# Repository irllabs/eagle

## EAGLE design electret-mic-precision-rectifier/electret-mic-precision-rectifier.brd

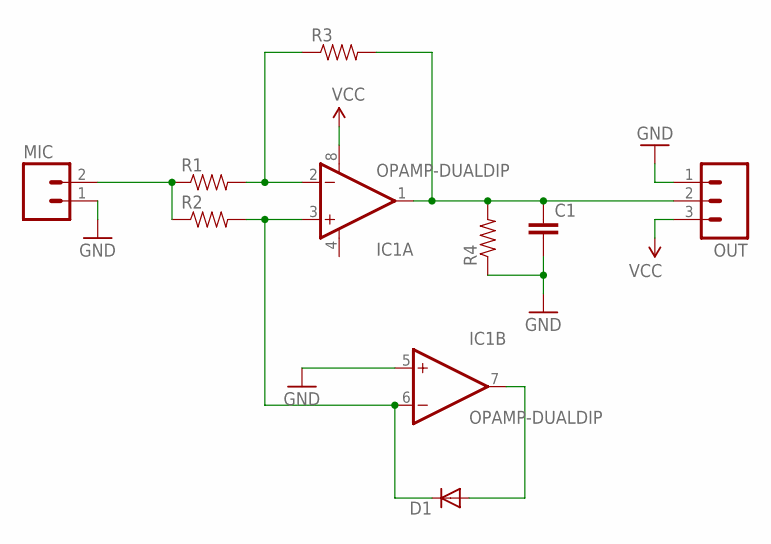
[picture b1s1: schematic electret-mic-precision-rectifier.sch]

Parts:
C1: CAP_; AXIAL-5MM
D1: DIODEPTH; DIODE-1N4001
IC1: OPAMP-DUALDIP; DIP08
MIC: M02PTH; 1X02
OUT: M03PTH; 1X03
R1, R2, R3, R4: RESISTORPTH-1/6W; 1/6W-RES

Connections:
GND: C1.P$2 (2), IC1.5 (+IN), MIC.1, OUT.1, R4.1
unnamed: C1.P$1 (1), IC1.1 (OUT), OUT.2, R3.2, R4.2
unnamed: IC1.2 (-IN), R1.2, R3.1
unnamed: D1.C, IC1.3 (+IN), IC1.6 (-IN), R2.2
unnamed: D1.A, IC1.7 (OUT)
unnamed: MIC.2, R1.1, R2.1
V-: IC1.4 (V-)
VCC: IC1.8 (V+), OUT.3

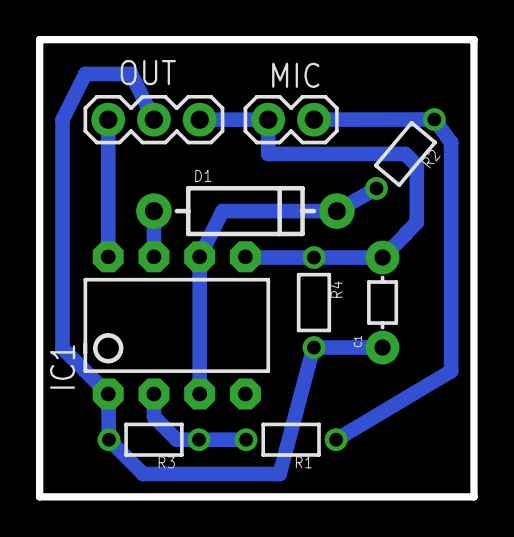
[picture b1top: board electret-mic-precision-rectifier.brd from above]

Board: 2 copper layers, 24.1 x 25.4 mm, 9 parts (0 on the bottom side), 7 nets.

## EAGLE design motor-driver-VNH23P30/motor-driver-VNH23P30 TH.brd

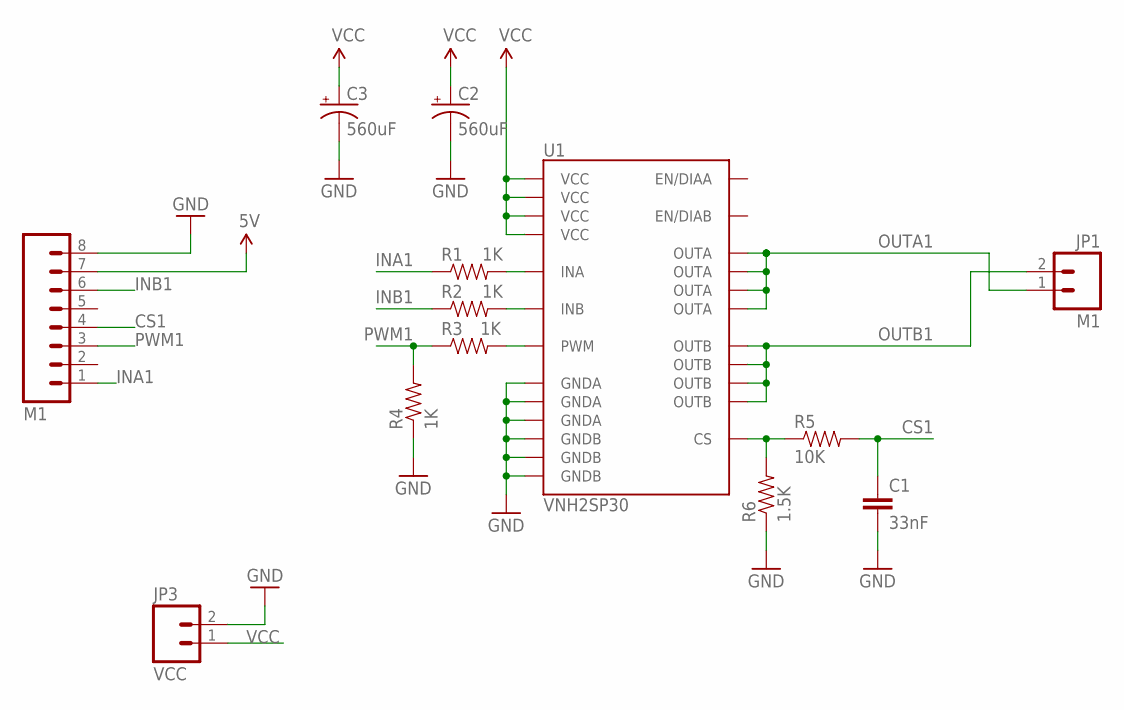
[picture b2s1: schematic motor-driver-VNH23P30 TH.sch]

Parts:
C1: 33nF; CAP-PTH-SMALLEZ
C2, C3: 560uF; CPOL-RADIAL-1000UF-25V
JP1: M1; 1X02_XTRA_BIG
JP3: VCC; 1X02_XTRA_BIG
P: M1; 1X08
R1, R2, R3, R4: 1K; 1/6W-RES
R5: 10K; 1/6W-RES
R6: 1.5K; 1/6W-RES
U1: VNH2SP30

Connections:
5V: P.7
CS1: C1.1, P.4, R5.2
GND: C1.2, C2.2 (-), C3.2 (-), JP3.2, P.8, R4.1, R6.1, U1.18 (GNDB), U1.19 (GNDB), U1.20 (GNDB), U1.26 (GNDA), U1.27 (GNDA), U1.28 (GNDA)
INA1: P.1, R1.1
INB1: P.6, R2.1
unnamed: R2.2, U1.11 (INB)
unnamed: R1.2, U1.5 (INA)
unnamed: R3.2, U1.8 (PWM)
unnamed: R5.1, R6.2, U1.9 (CS)
OUTA1: JP1.1, U1.1 (OUTA), U1.25 (OUTA), U1.30 (OUTA), U1.SLUG3 (OUTA)
OUTB1: JP1.2, U1.15 (OUTB), U1.16 (OUTB), U1.21 (OUTB), U1.SLUG2 (OUTB)
PWM1: P.3, R3.1, R4.2
VCC: C2.1 (+), C3.1 (+), JP3.1, U1.3 (VCC), U1.13 (VCC), U1.23 (VCC), U1.SLUG1 (VCC)

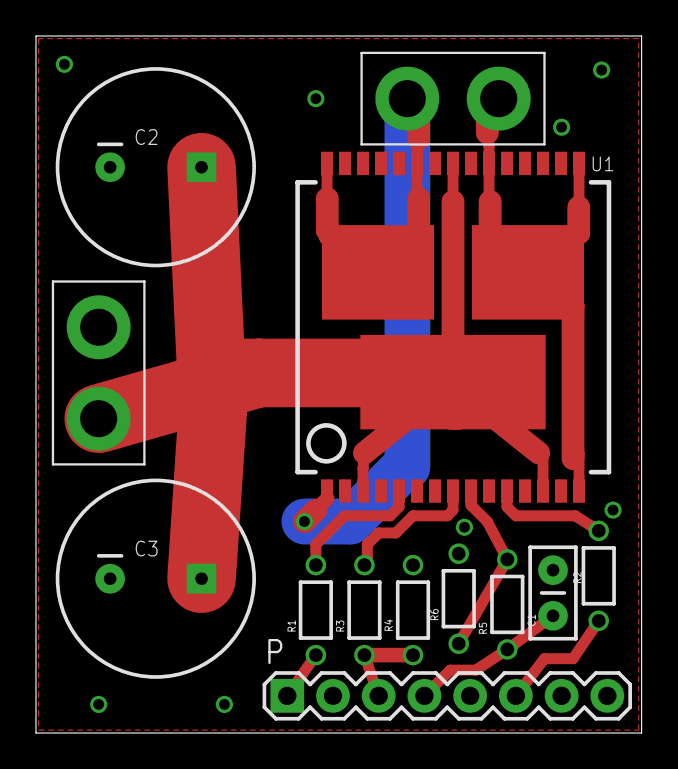
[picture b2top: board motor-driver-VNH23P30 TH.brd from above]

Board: 2 copper layers, 33.6 x 38.7 mm, 13 parts (0 on the bottom side), 12 nets.

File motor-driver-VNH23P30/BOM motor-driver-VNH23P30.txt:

Partlist exported from C:/Users/Spencer Barton/Dropbox/CMU/Activities/eagle/Spencer's Updates/motor-driver-VNH23P30/motor-driver-VNH23P30.sch at 6/30/2013 11:42:02 AM

Assembly variant: 

Part Value    Device       Package       Description        
C1   33nF     CAP1206      1206          Capacitor          
C2   560uF    CAP_POLG     PANASONIC_G   Capacitor Polarized
C3   560uF    CAP_POLG     PANASONIC_G   Capacitor Polarized
JP1  M1       M02PTH4      1X02_XTRA_BIG Header 2           
JP3  VCC      M02PTH4      1X02_XTRA_BIG Header 2           
P    M1       M081X08      1X08          Header 8           
R1   1K       RESISTOR1206 1206          Resistor           
R2   1K       RESISTOR1206 1206          Resistor           
R3   1K       RESISTOR1206 1206          Resistor           
R4   1K       RESISTOR1206 1206          Resistor           
R5   10K      RESISTOR1206 1206          Resistor           
R6   1.5K     RESISTOR1206 1206          Resistor           
U1   VNH2SP30 VNH2SP30     VNH2SP30

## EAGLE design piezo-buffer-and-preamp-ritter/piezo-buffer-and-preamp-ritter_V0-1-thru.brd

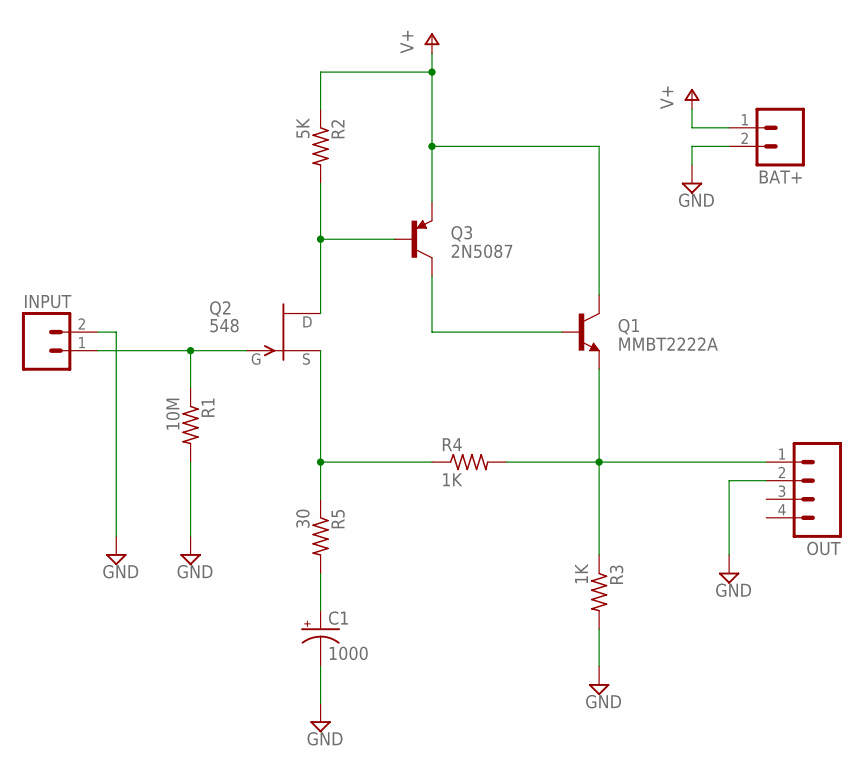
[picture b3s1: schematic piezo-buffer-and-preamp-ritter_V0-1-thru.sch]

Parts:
BAT+: M02LOCK; 1X02_LOCK
C1: 1000; CPOL-RADIAL-10UF-25V
INPUT: M02LOCK; 1X02_LOCK
OUT: M04PTH; 1X04
Q1: MMBT2222A; TO-92
Q2: 548; TO-92
Q3: 2N5087; TO-92
R1: 10M; VMTA55
R2: 5K; VMTA55
R3, R4: 1K; VMTA55
R5: 30; VMTA55

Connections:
GND: BAT+.2, C1.2 (-), INPUT.2, OUT.2, R1.2, R3.2
unnamed: INPUT.1, Q2.1 (G), R1.1
unnamed: Q2.3 (D), Q3.2 (B), R2.2
unnamed: OUT.1, Q1.1 (E), R3.1, R4.2
unnamed: Q2.2 (S), R4.1, R5.1
unnamed: Q1.2 (B), Q3.3 (C)
unnamed: C1.1 (+), R5.2
V+: BAT+.1, Q1.3 (C), Q3.1 (E), R2.1

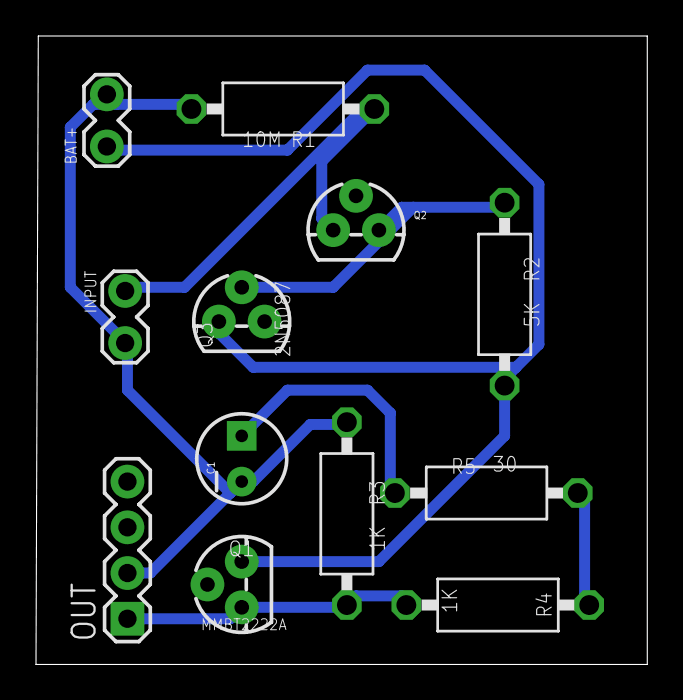
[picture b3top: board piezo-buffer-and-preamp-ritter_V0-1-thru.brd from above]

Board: 2 copper layers, 34.0 x 34.9 mm, 12 parts (0 on the bottom side), 8 nets.

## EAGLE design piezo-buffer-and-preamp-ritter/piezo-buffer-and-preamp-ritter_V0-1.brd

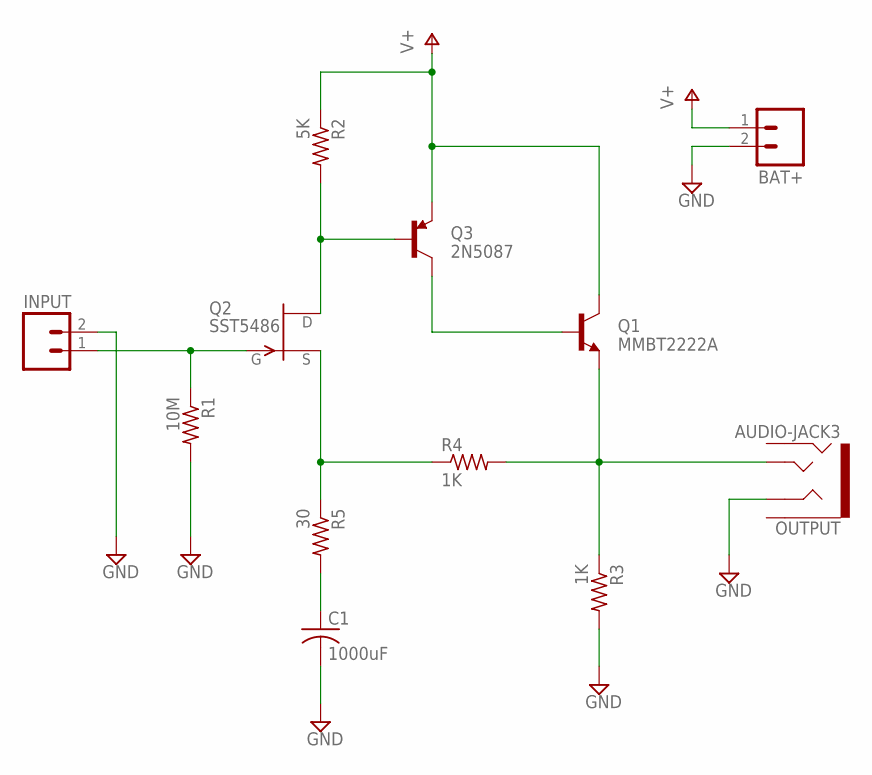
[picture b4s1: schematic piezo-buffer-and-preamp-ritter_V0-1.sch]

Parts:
BAT+: M02LOCK; 1X02_LOCK
C1: 1000uF; C0805
INPUT: M02LOCK; 1X02_LOCK
OUTPUT: AUDIO-JACK3; AUDIO-JACK-TRRS-SMD
Q1: MMBT2222A; SOT23
Q2: SST5486; SOT23
Q3: 2N5087; SOT23
R1: 10M; R0805
R2: 5K; R0805
R3, R4: 1K; R0805
R5: 30; R0805

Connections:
GND: BAT+.2, C1.2, INPUT.2, OUTPUT.RING1, R1.2, R3.2
unnamed: INPUT.1, Q2.3 (G), R1.1
unnamed: Q2.1 (D), Q3.1 (B), R2.2
unnamed: OUTPUT.TIP, Q1.2 (E), R3.1, R4.2
unnamed: Q2.2 (S), R4.1, R5.1
unnamed: Q1.1 (B), Q3.3 (C)
unnamed: C1.1, R5.2
V+: BAT+.1, Q1.3 (C), Q3.2 (E), R2.1

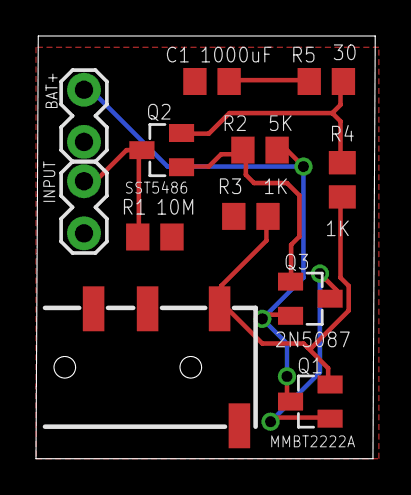
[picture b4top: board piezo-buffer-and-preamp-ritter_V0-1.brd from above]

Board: 2 copper layers, 18.8 x 23.5 mm, 12 parts (0 on the bottom side), 8 nets.

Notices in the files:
parts and their libraries:
SparkFun-AnalogIC: Licensing: CC v3.0 Share-Alike You are welcome to use this library for commercial purposes.
SparkFun-Connectors: Licensing: Creative Commons ShareAlike 4.0 International - https://creativecommons.org/licenses/by-sa/4.0
